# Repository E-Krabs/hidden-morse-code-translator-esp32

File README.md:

# hidden-morse-code-translator-esp32

Translates morse from buttons under toes and vibrates target language's result via Google Translate.<br>
<h3>Usage</h3>
<p>Input:<br>
Uses two buttons placed under the big toes. Use the left button (key) to input either a dot or a dash. Use the right button (ctrl) to input a 1 space between letters, or 2 spaces between words. Holding down the control key submits the query for translation. Holding it down longer clears the input.</p>
<p>Output:<br>
After sending the encoded word in the source language to the API for translation, the target language translation will be re-encoded back into morse and vibrate on the user's leg or foot for interpretation.</p>
<h3>Gallery</h3>
<div display
</img>

<table>
  <tr>
    <td>
      
    </td>
    <td>
      
    </td>
    <td>
      
    </td>
  </tr>
  <tr>
        <td>
      
    </td>
    <td>
      
    </td>
  </tr>
</table>
<h3>Parts</h3>
<ul>
  <li>Any esp32 with micropython (https://www.amazon.com/HiLetgo-ESP-32S-Bluetooth-Wireless-ESP-WROOM-32/dp/B077KJNVFP/)</li>
  <li>2x Buttons (<href src="https://www.aliexpress.us/item/3256801735655471.html?spm=a2g0o.productlist.main.5.6dc118edIIAnYi&algo_pvid=07669b71-7154-402e-83de-f07114f854c0&algo_exp_id=07669b71-7154-402e-83de-f07114f854c0-2&pdp_npi=3%2540dis!USD!1.80!1.62!!!1.80!!">https://www.aliexpress.us/item/3256801735655471.html</href>)</li>
  <li>LiPo 3.7V 1500mAh Battery (www.amazon.com/EEMB-Battery-Rechargeable-Connector-Certified/dp/B09DPMS6HN) <b>Swap Polarity!</b></li>
  <li>Vibration Motor (www.amazon.com/DZS-Elec-Button-type-Electronics-Appliances/dp/B07PHRX7QH)</li>
</ul>

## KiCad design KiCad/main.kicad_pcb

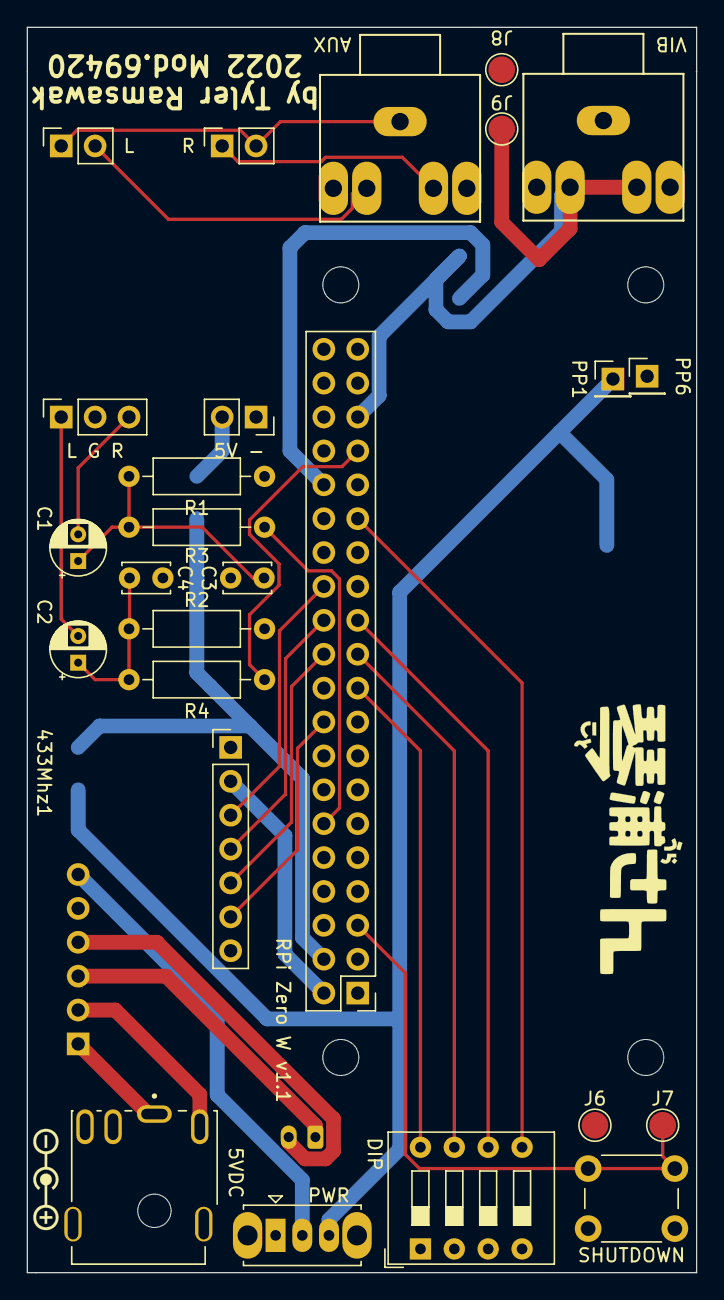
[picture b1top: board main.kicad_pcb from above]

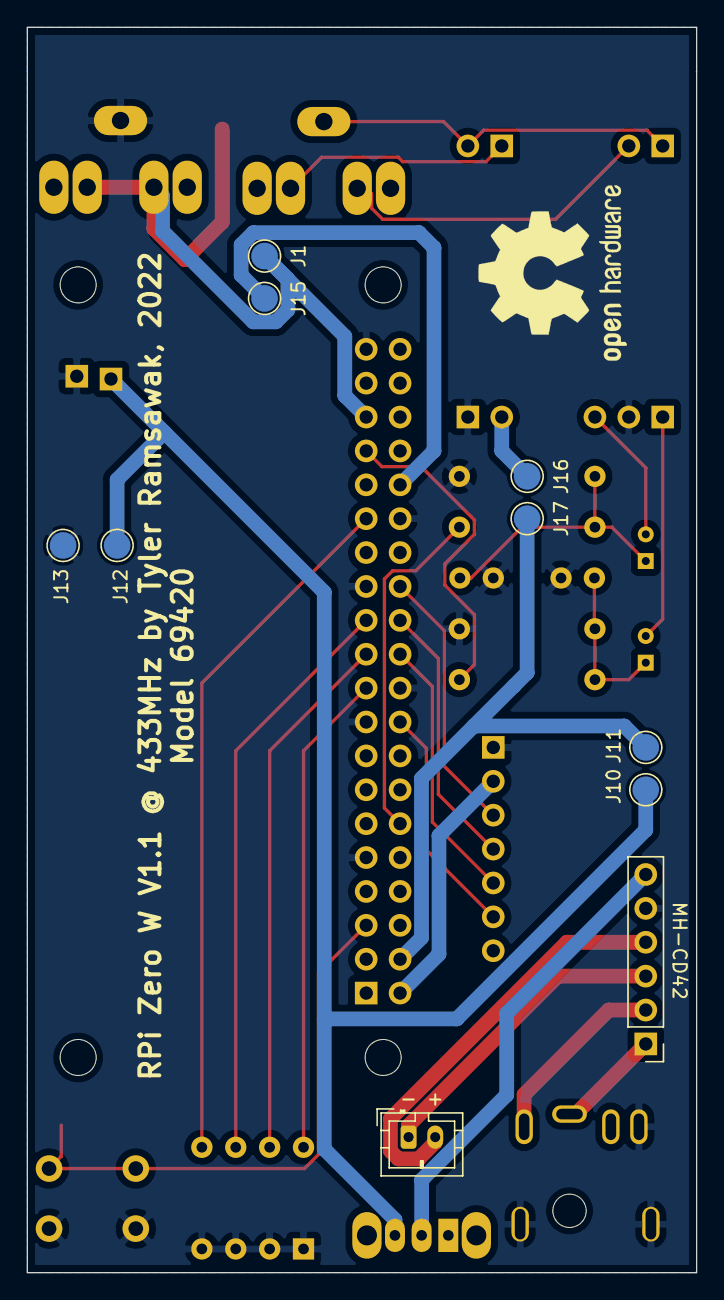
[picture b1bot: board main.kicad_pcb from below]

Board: 2 copper layers, 50.2 x 93.3 mm, 36 parts (10 on the bottom side), 30 nets.

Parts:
5V -: Conn_01x02_Male; PinSocket_1x02_P2.54mm_Vertical
5VDC: PJ-085H; CUI_PJ-085
433Mhz1: rfpt2272-m4; PinHeader_1x07_P2.54mm_Vertical
- +: Conn_01x02_Female; JST_PH_B2B-PH-K_1x02_P2.00mm_Vertical
AUX: AudioJack3_Dual_Ground_Switch; PJ_307
C1, C2: 10u; CP_Radial_D4.0mm_P2.00mm
C3, C4: 33n; C_Disc_D3.4mm_W2.1mm_P2.50mm
DIP: SW_DIP_x04; SW_DIP_SPSTx04_Slide_9.78x12.34mm_W7.62mm_P2.54mm
J1, J6, J7, J8, J9, J10, J11, J12, J13, J15, J16, J17: Conn_01x01_Male; TestPoint_Pad_D2.0mm
L: Conn_01x02_Male; PinSocket_1x02_P2.54mm_Vertical
L G R: Conn_01x03_Male; PinSocket_1x03_P2.54mm_Vertical
MH-CD42: MH-CD42P-PCB; PinHeader_1x06_P2.54mm_Vertical
PP1, PP6: Conn_01x01; PinHeader_1x01_P2.54mm_Vertical
PWR: SW_SPDT; SW_Slide_1P2T_CK_OS102011MS2Q
R: Conn_01x02_Male; PinSocket_1x02_P2.54mm_Vertical
R1, R2: 150R; R_Axial_DIN0207_L6.3mm_D2.5mm_P10.16mm_Horizontal
R3, R4: 270R; R_Axial_DIN0207_L6.3mm_D2.5mm_P10.16mm_Horizontal
RPi Zero W v1.1: RPiZeroWGPIO; PinHeader_2x20_P2.54mm_Vertical
SHUTDOWN: SW_Push; SW_PUSH_6mm_H5mm
VIB: AudioJack3_Dual_Ground_Switch; PJ_307

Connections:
GND: 5V -.1, 5VDC.2, 5VDC.S1, 5VDC.S2, 433Mhz1.1, C3.1, C4.1, DIP.1, DIP.2, DIP.3, DIP.4, J6.1, J8.1, J13.1, L G R.2, MH-CD42.5, PP6.1, R1.1, R2.2, RPi Zero W v1.1.6, RPi Zero W v1.1.9, RPi Zero W v1.1.14, RPi Zero W v1.1.17, RPi Zero W v1.1.20, RPi Zero W v1.1.25, RPi Zero W v1.1.30, RPi Zero W v1.1.34, RPi Zero W v1.1.39, SHUTDOWN.1, VIB.1
unnamed: 433Mhz1.2, RPi Zero W v1.1.2
unnamed: 433Mhz1.3, RPi Zero W v1.1.26
unnamed: 433Mhz1.4, RPi Zero W v1.1.24
unnamed: 433Mhz1.5, RPi Zero W v1.1.22
unnamed: 433Mhz1.6, RPi Zero W v1.1.18
unnamed: AUX.1, L.1, R.2
unnamed: AUX.4, L.2
unnamed: AUX.5, R.1
unnamed: C1.1, C3.2, R1.2, R3.2
unnamed: C1.2, L G R.3
unnamed: C2.1, C4.2, R2.1, R4.2
unnamed: C2.2, L G R.1
unnamed: J1.1, J9.1, RPi Zero W v1.1.35, VIB.4, VIB.5
unnamed: J7.1, RPi Zero W v1.1.5, SHUTDOWN.2
unnamed: J10.1, J12.1, PP1.1, PWR.3
unnamed: J11.1, J17.1, RPi Zero W v1.1.4
unnamed: 5VDC.1, MH-CD42.1
unnamed: 5VDC.4, MH-CD42.2
unnamed: J15.1, RPi Zero W v1.1.32
unnamed: 5V -.2, J16.1
unnamed: - +.1, MH-CD42.3
unnamed: - +.2, MH-CD42.4
unnamed: R3.1, RPi Zero W v1.1.12
unnamed: R4.1, RPi Zero W v1.1.33
unnamed: DIP.5, RPi Zero W v1.1.29
unnamed: DIP.6, RPi Zero W v1.1.23
unnamed: DIP.7, RPi Zero W v1.1.21
unnamed: DIP.8, RPi Zero W v1.1.19
unnamed: MH-CD42.6, PWR.2
